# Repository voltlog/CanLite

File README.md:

# Voltlog CanLite
This repository contains the source files for the CanLite, an ESP32 based CAN development/hacking board which features a built-in automotive grade dc-dc converter as well as an optional two channel high-side automotive grade switch capable of switching up to 1.8A per channel with plenty of protection features.

More info about this project in [Voltlog #370](https://youtu.be/DLKQcw506ck) & [Voltlog #390](https://youtu.be/_m2UW_pron4).
If you would like to order one of these boards ready assembled, check out my [Tindie store](https://voltlog.com/y/canlite).

### Changelog
- revD: Switched to a different inductor, [different high-side switch](https://www.infineon.com/dgdl/Infineon-BTS452T-DS-v01_01-EN.pdf?fileId=5546d4625a888733015aa9afaf0f35d1), optimised layout.
- revC: Switched to a different inductor pn, added some IO access via test points.
- revB: Fixed some bugs from revA.
- revA: Initial release.

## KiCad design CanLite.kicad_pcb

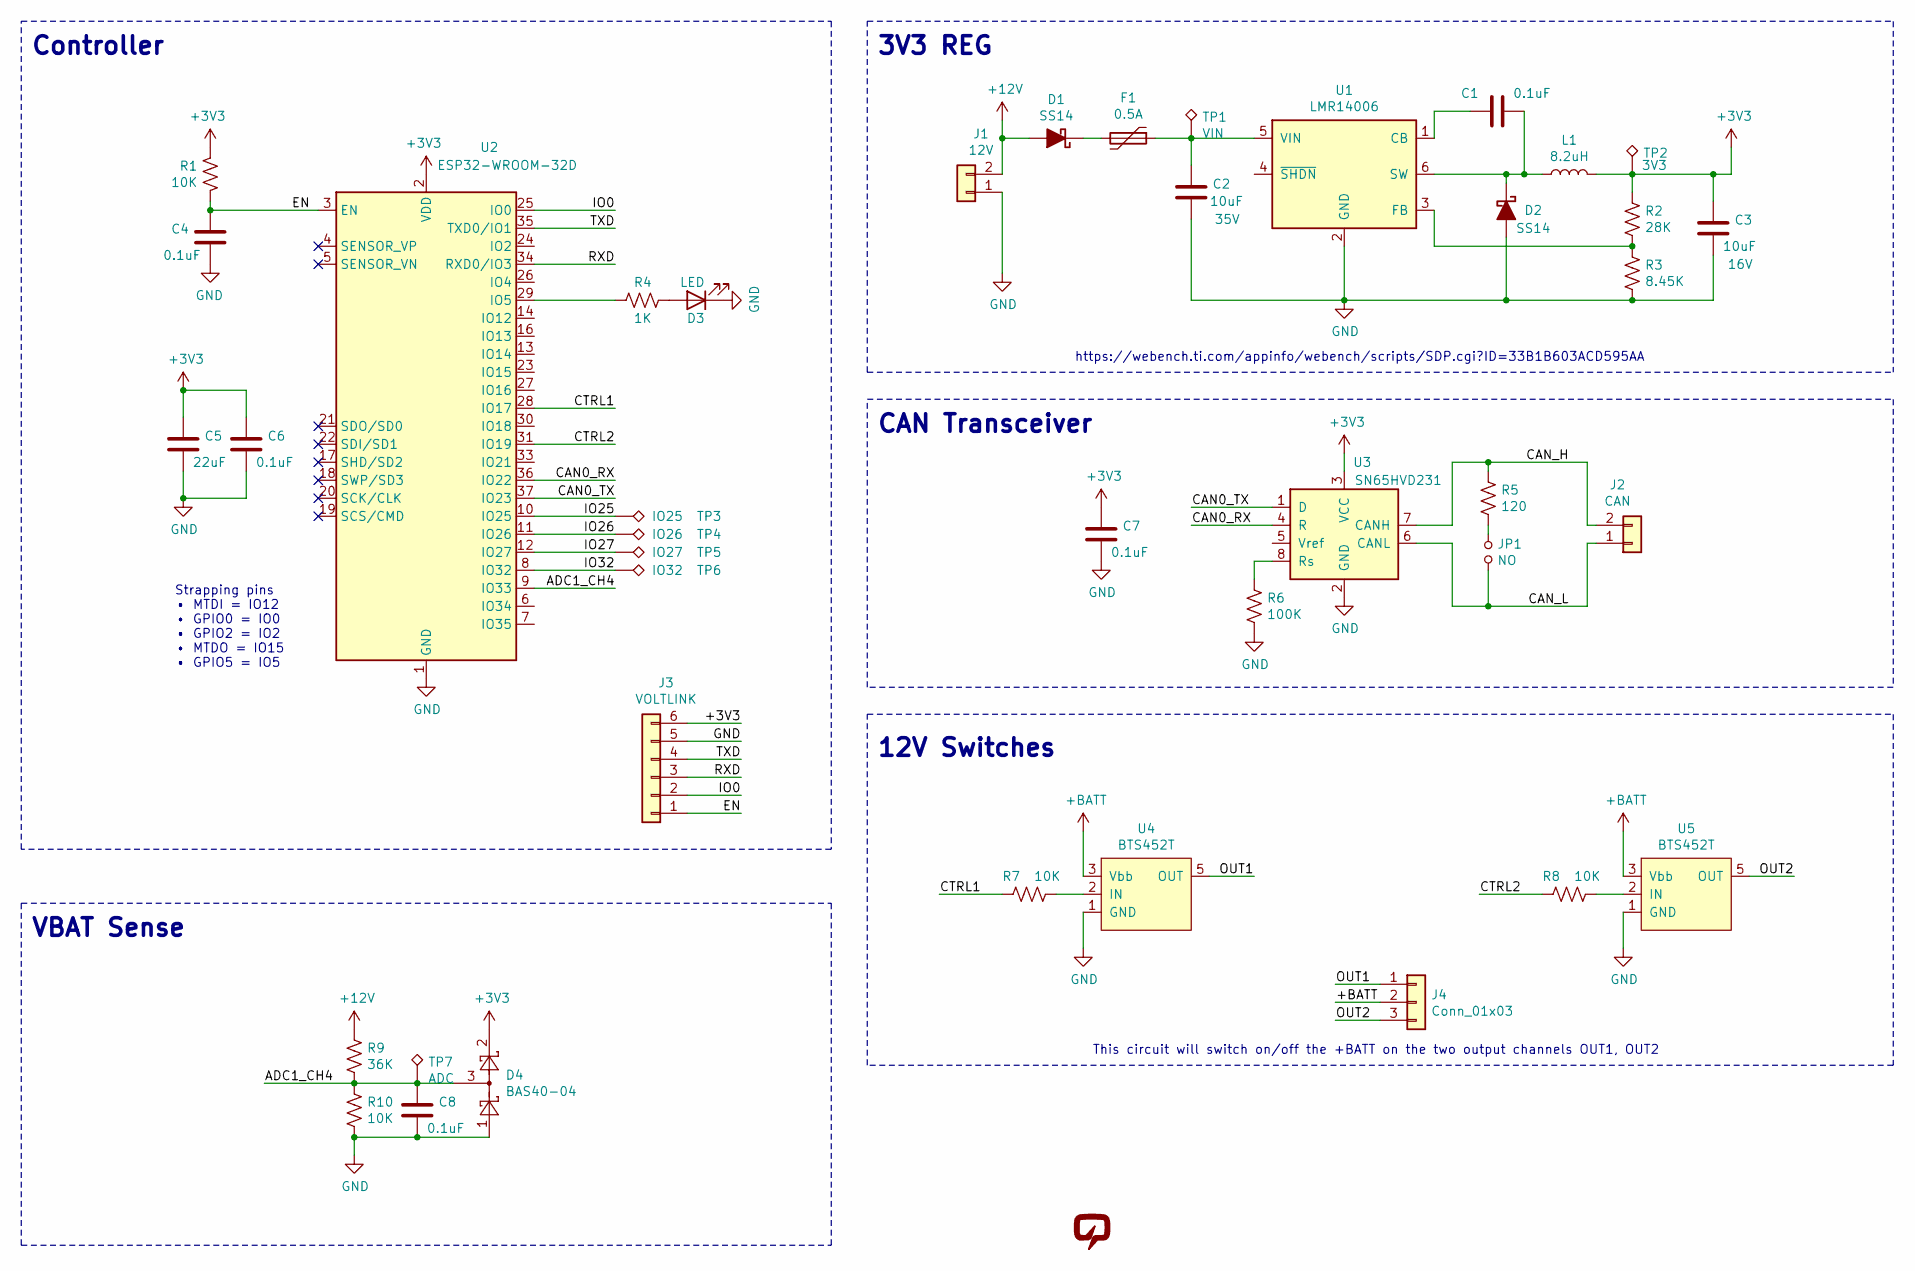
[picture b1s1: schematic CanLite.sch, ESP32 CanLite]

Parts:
C1, C4, C6, C7, C8: 0.1uF; C_0603_1608Metric
C2: 10uF; C_1206_3216Metric; Voltage 35V; LCSC C391262
C3: 10uF; C_1206_3216Metric; Voltage 16V; LCSC C408152
C5: 22uF; C_1206_3216Metric; LCSC C408152
D1, D2: SS14; D_SMA
D3: LED; LED_0603_1608Metric
D4: BAS40-04; SOT-23
F1: 0.5A; Fuse_1812_4532Metric; LCSC C262024
J1: 12V; TerminalBlock_RND_205-00232_1x02_P5.08mm_Horizontal
J2: CAN; TerminalBlock_RND_205-00232_1x02_P5.08mm_Horizontal
J3: VOLTLINK; JST_SH_BM06B-SRSS-TB_1x06-1MP_P1.00mm_Vertical
J4: Conn_01x03; TerminalBlock_RND_205-00233_1x03_P5.08mm_Horizontal
JP1: NO; SolderJumper-2_P1.3mm_Open_TrianglePad1.0x1.5mm
L1: 8.2uH; Inductor_7.5x6.6; LCSC C436550
R1, R7, R8, R10: 10K; R_0603_1608Metric
R2: 28K; R_0603_1608Metric
R3: 8.45K; R_0603_1608Metric
R4: 1K; R_0603_1608Metric
R5: 120; R_1210_3225Metric
R6: 100K; R_0603_1608Metric
R9: 36K; R_0603_1608Metric
TP1: VIN; TestPoint_Pad_D1.0mm
TP2: 3V3; TestPoint_Pad_D1.0mm
TP3: IO25; TestPoint_Pad_D1.0mm
TP4: IO26; TestPoint_Pad_D1.0mm
TP5: IO27; TestPoint_Pad_D1.0mm
TP6: IO32; TestPoint_Pad_D1.0mm
TP7: ADC; TestPoint_Pad_D1.0mm
U1: LMR14006; SOT-23-6
U2: ESP32-WROOM-32D; ESP32-WROOM-32
U3: SN65HVD231; SOIC-8_3.9x4.9mm_P1.27mm
U4, U5: BTS452T; TO-252-4
V1: VOLTLOG_LOGO; voltlog_mask_3mm

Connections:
+3V3: C3.1, C5.1, C6.1, C7.1, D4.2, J3.6, L1.2, R1.1, R2.1, TP2.1, U2.2 (VDD), U3.3 (VCC)
+12V: D1.2 (A), J1.2, R9.1
+BATT: J4.2, U4.3 (Vbb), U5.3 (Vbb)
/ADC1_CH4: C8.1, D4.3, R9.2, R10.1, TP7.1, U2.9 (IO33)
/CAN0_RX: U2.36 (IO22), U3.4 (R)
/CAN0_TX: U2.37 (IO23), U3.1 (D)
/CAN_H: J2.2, R5.1, U3.7 (CANH)
/CAN_L: J2.1, JP1.2, U3.6 (CANL)
/CTRL1: R7.2, U2.28 (IO17)
/CTRL2: R8.2, U2.31 (IO19)
/EN: C4.1, J3.1, R1.2, U2.3 (EN)
/IO0: J3.2, U2.25 (IO0)
/IO25: TP3.1, U2.10 (IO25)
/IO26: TP4.1, U2.11 (IO26)
/IO27: TP5.1, U2.12 (IO27)
/IO32: TP6.1, U2.8 (IO32)
/OUT1: J4.1, U4.5 (OUT)
/OUT2: J4.3, U5.5 (OUT)
/RXD: J3.3, U2.34 (RXD0/IO3)
/TXD: J3.4, U2.35 (TXD0/IO1)
GND: C2.2, C3.2, C4.2, C5.2, C6.2, C7.2, C8.2, D2.2 (A), D3.1 (K), D4.1, J1.1, J3.5, R3.2, R6.2, R10.2, U1.2 (GND), U2.1 (GND), U2.15 (GND), U2.38 (GND), U2.39 (GND), U3.2 (GND), U4.1 (GND), U5.1 (GND)
unnamed: C1.1, U1.1 (CB)
unnamed: C1.2, D2.1 (K), L1.1, U1.6 (SW)
unnamed: C2.1, F1.1, TP1.1, U1.5 (VIN)
unnamed: D1.1 (K), F1.2
unnamed: D3.2 (A), R4.1
unnamed: JP1.1, R5.2
unnamed: R2.2, R3.1, U1.3 (FB)
unnamed: R4.2, U2.29 (IO5)
unnamed: R6.1, U3.8 (Rs)
unnamed: R7.1, U4.2 (IN)
unnamed: R8.1, U5.2 (IN)

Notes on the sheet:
Strapping pins • MTDI = IO12 • GPIO0 = IO0 • GPIO2 = IO2 • MTDO = IO15 • GPIO5 = IO5
This circuit will switch on/off the +BATT on the two output channels OUT1, OUT2
https://webench.ti.com/appinfo/webench/scripts/SDP.cgi?ID=33B1B603ACD595AA
Controller
VBAT Sense
3V3 REG
CAN Transceiver
12V Switches

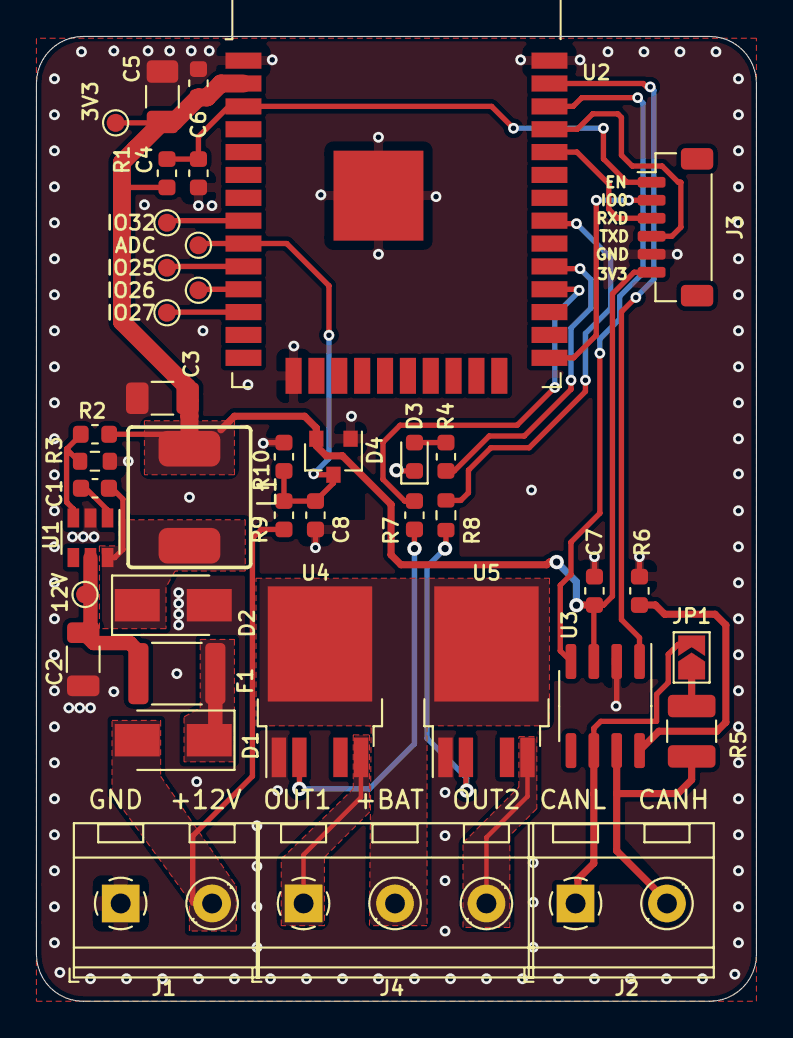
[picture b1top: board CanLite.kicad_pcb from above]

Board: 2 copper layers, 40.0 x 53.6 mm, 42 parts (0 on the bottom side), 32 nets.

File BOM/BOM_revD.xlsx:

Qty | Reference(s) | Value | Footprint | Datasheet | LCSC | PN | Voltage
5 | C1, C4, C6, C7, C8 | 0.1uF | Capacitor_SMD:C_0603_1608Metric | ~
2 | C2, C3 | 10uF | Capacitor_SMD:C_1206_3216Metric | https://datasheet.lcsc.com/szlcsc/1912111437_Murata-Electron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 | C391262 | GRM21BR61E106MA73L | 35V
1 | C5 | 22uF | Capacitor_SMD:C_1206_3216Metric | https://datasheet.lcsc.com/szlcsc/1912111437_Murata-Electron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 | C408152 | GRM31CR70J226KE19L
2 | D1, D2 | SS14 | Diode_SMD:D_SMA | ~
1 | D3 | LED | LED_SMD:LED_0603_1608Metric | ~
1 | D4 | BAS40-04 | Package_TO_SOT_SMD:SOT-23 | http://www.vishay.com/docs/85701/bas40v.pdf
1 | F1 | 0.5A | Fuse:Fuse_1812_4532Metric | https://datasheet.lcsc.com/szlcsc/1809292114_TLC-Electronic-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 | C262024 | TLC-MSMD075
1 | J1 | 12V | TerminalBlock_RND:TerminalBlock_RND_205-00232_1x02_P5.08mm_Horizontal | ~
1 | J2 | CAN | TerminalBlock_RND:TerminalBlock_RND_205-00232_1x02_P5.08mm_Horizontal | ~
1 | J3 | VOLTLINK | Connector_JST:JST_SH_BM06B-SRSS-TB_1x06-1MP_P1.00mm_Vertical | ~
1 | J4 | Conn_01x03 | TerminalBlock_RND:TerminalBlock_RND_205-00233_1x03_P5.08mm_Horizontal | ~
1 | JP1 | NO | Jumper:SolderJumper-2_P1.3mm_Open_TrianglePad1.0x1.5mm | ~
1 | L1 | 8.2uH | voltlog:Inductor_7.5x6.6 |  | C436550 | PSPMAA0603-8R2M-ANF
4 | R1, R7, R8, R10 | 10K | Resistor_SMD:R_0603_1608Metric | ~
1 | R2 | 28K | Resistor_SMD:R_0603_1608Metric | ~
1 | R3 | 8.45K | Resistor_SMD:R_0603_1608Metric | ~
1 | R4 | 1K | Resistor_SMD:R_0603_1608Metric | ~
1 | R5 | 120 | Resistor_SMD:R_1210_3225Metric | ~
1 | R6 | 100K | Resistor_SMD:R_0603_1608Metric | ~
1 | R9 | 36K | Resistor_SMD:R_0603_1608Metric | ~
1 | U1 | LMR14006 | Package_TO_SOT_SMD:SOT-23-6 | https://www.ti.com/lit/ds/symlink/lmr14006.pdf?ts=1611109108480
1 | U2 | ESP32-WROOM-32 | RF_Module:ESP32-WROOM-32 | https://www.espressif.com/sites/default/files/documentation/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
1 | U3 | SN65HVD231 | Package_SO:SOIC-8_3.9x4.9mm_P1.27mm | http://www.ti.com/lit/ds/symlink/sn65hvd230.pdf
2 | U4, U5 | BTS452T | Package_TO_SOT_SMD:TO-252-4 | https://www.infineon.com/dgdl/Infineon-BTS452T-DS-v01_01-EN.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

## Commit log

2021-09-14 upload image
2021-11-16 Released rev.D
2021-11-16 Updated readme rev.D
2022-02-08 Migrated project to Kicad V6
2022-02-08 Added user contributed 3d printed case design
2022-04-08 Added CAN Receive example code
